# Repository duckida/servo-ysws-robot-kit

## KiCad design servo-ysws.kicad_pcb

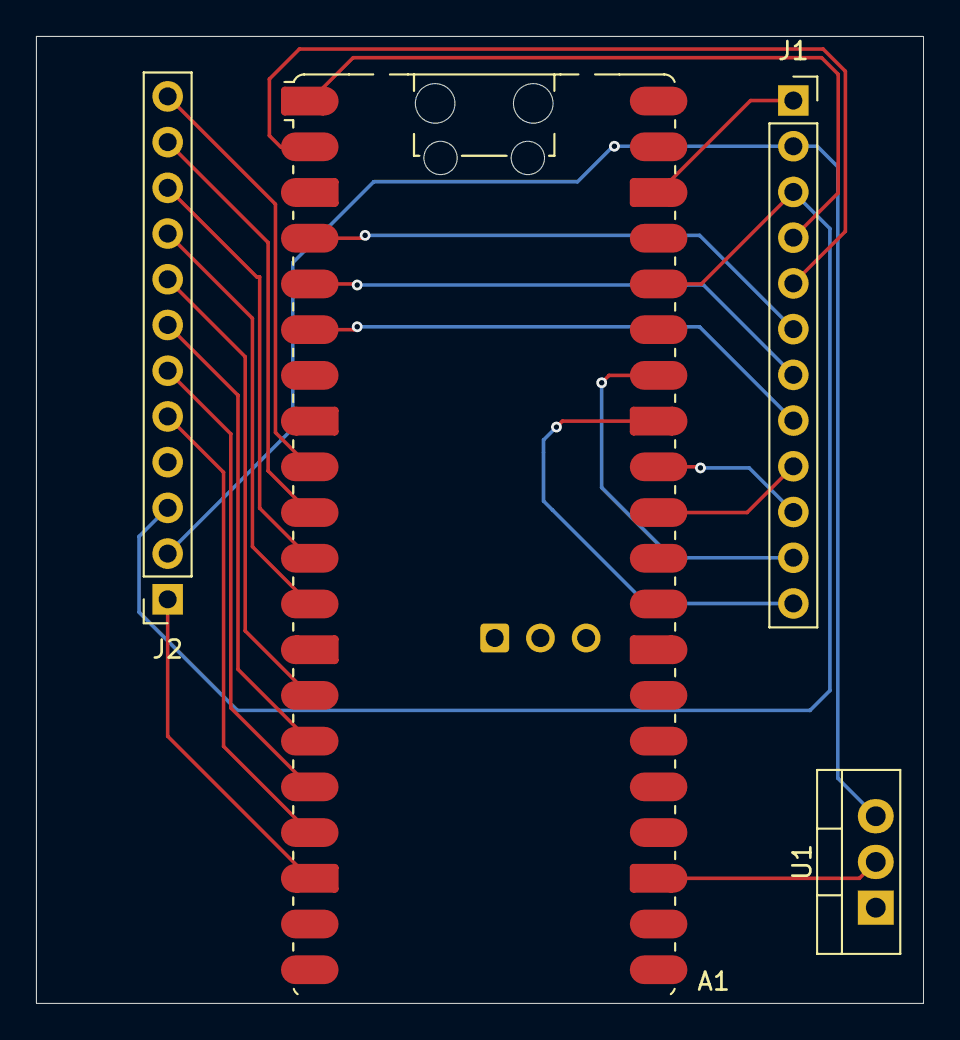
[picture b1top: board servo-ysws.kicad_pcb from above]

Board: 2 copper layers, 49.3 x 53.7 mm, 4 parts (0 on the bottom side), 21 nets.

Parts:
A1: RaspberryPi_Pico_W; RaspberryPi_Pico_W_SMD_HandSolder
J1: Conn_01x12_Socket (front connector); PinSocket_1x12_P2.54mm_Vertical
J2: Conn_01x12_Socket (back connector); PinSocket_1x12_P2.54mm_Vertical
U1: L7805 9V->️5V regulator; TO-220-3_Vertical

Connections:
+3V3: A1.36 (3V3), J1.3, J2.3
+5V: A1.39 (VSYS), J1.2, J2.2, U1.3 (OUT)
/A0: A1.31 (GPIO26_ADC0), J1.9
/A1: A1.32 (GPIO27_ADC1), J1.10
/A2: A1.34 (GPIO28_ADC2), J1.11
/GP0: A1.1 (GPIO0), J1.4
/GP1: A1.2 (GPIO1), J1.5
/GP2: A1.4 (GPIO2), J1.6
/GP3: A1.5 (GPIO3), J1.7
/GP4: A1.6 (GPIO4), J1.8
/GP5: A1.7 (GPIO5), J2.4
/GP6: A1.17 (GPIO13), J2.5
/GP7: A1.16 (GPIO12), J2.6
/GP8: A1.15 (GPIO11), J2.7
/GP9: A1.14 (GPIO10), J2.8
/GP10: A1.12 (GPIO9), J2.9
/GP11: A1.11 (GPIO8), J2.10
/GP12: A1.10 (GPIO7), J2.11
/GP13: A1.9 (GPIO6), J2.12
GND: A1.3 (GND), A1.8 (GND), A1.13 (GND), A1.18 (GND), A1.23 (GND), A1.28 (GND), A1.38 (GND), J1.1, J2.1, U1.2 (GND)
GNDA: A1.33 (AGND), J1.12
